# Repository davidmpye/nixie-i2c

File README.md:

# nixie-i2c

Nixie-I2C is a collection of PCB designs and accompanying library designed to simplify using [Nixie tubes](http://en.wikipedia.org/wiki/Nixie_tube) with Arduino and ESP8266 based boards (and perhaps others in future).

## Design

Driving nixie tubes from microcontrollers can present several issues:
 - Can rely on expensive/obsolute/irreplacable Soviet-era driver ICs (eg K155ID1)
 - Or, if you drive the cathodes directly, requires a large number of pins from the microcontroller (e.g a numeric IN-14 nixie tube has 12 cathodes - 0-9 and left/right decimal places), so it becomes difficult to direct-drive multiple tubes without running out of IO pins
 - If using the 'direct drive' solution above, you need a high-voltage capable transistor per cathode.
 
The main idea of this project is to provide a convenient driver board for a nixie tube, allowing it to be controlled from the microcontroller via I2C.

## Features

The PCB design here (which is tested and works) offers the following features:
 - Bus based (I2C) - put all your tubes in a row on stripboard or similar!
 - Designed for IN-14 nixie tube
 - I2C address (3-bit) settable (solder-pads on underside of board), allowing 9 nixie tubes per I2C bus.
 - Handles all HV switching, allowing a simple library interface to select the digit to be displayed.  Uses cheap SMD NPN transistors (MMBTA42s)
 - Has option for installing a programmable RGB (WS2812B) LED under the base of each tube, allowing bottom-lighting of any colour/brightness, without requiring ongoing control from the microcontroller (eg no PWM timing loops etc)
 - Eagle brd/sch files provided
 - Licenced under the OSHW framework
 
 There is an accompanying library, which supports:
 - Arduino or ESP8266
 - Simple interface to setting a tube's display digit / decimal point status
 - Slot-machine display for cathode protection
 - Direct drive for up to 9 tubes (per I2C bus), no multiplexing/timer loops from the microntroller required
 
##Example

 The library is designed to be simple and easy to use:
 ```
 Nixie_i2c nix0(0x00);
 nix0.slotMachineDisplayNumber(1);  //Tube now displays 1
 delay(1000);
 nix0.slotMachineDisplayNumber(9);  //Tube now displays 9
 ```

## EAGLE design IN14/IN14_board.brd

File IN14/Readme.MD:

#IN-14 Nixie Tube I2C PCB design

##Tech Specs:
- Overall dimensions: 24mm x  52.5mm
- Nixie tube centre point: 12mm (ie in the middle of the board in X), 12.3mm in from front edge
- Screw fixing centre 1: 3.25 from edge, 3.25 in from front of board
- Screw fixing centre 2: 3mm from other edge, 19.75mm in from front of board
- Screw hole size: M3
- Pinout(from front to rear):
- - +HV (~170VDC)
- - GND (Common between +HV and VCC)
- - LED_DATA_IN (signal 'in' to WS2812B)
- - LED_DATA_OUT (signal 'out' to next WS2812B in chain)
- - VCC (3.3-5VDC)
- - SCL  (single external 4k7 pull-UP resistor per bus advisable)
- - SDA  (single external 4k7 pull-UP resistor per bus advisable)

##Parts list:
###Top side of board:
- 1x IN-12 nixie tube
- 1x Nixie tube base (3d printable one available as STL file in this folder, with cutout for WS2812B LED)
- 1x WS2812B LED (optional but good!)
- 1x MCP23017 I2C multiplexer IC (SMD)
- 1x 0806 anode resistor 
- 3x 0604 4k7 SMD resistor arrays

##Hints

- Solder the resistor arrays in to place first (flood soldering works best)
- Solder the I2C multiplexer chips and other parts in to place
- Set the I2C address bits on the rear side of the board - bridging the middle and left pad sets the bit to 0, middle and right sets the bit to 1.  Bridging all three pins shorts VCC to GND!
- If mounting PCB to the case, it's best to use nylon bolts - reducing the risk of an electrical fault allowing the anode voltage appearing on the outside of a case!

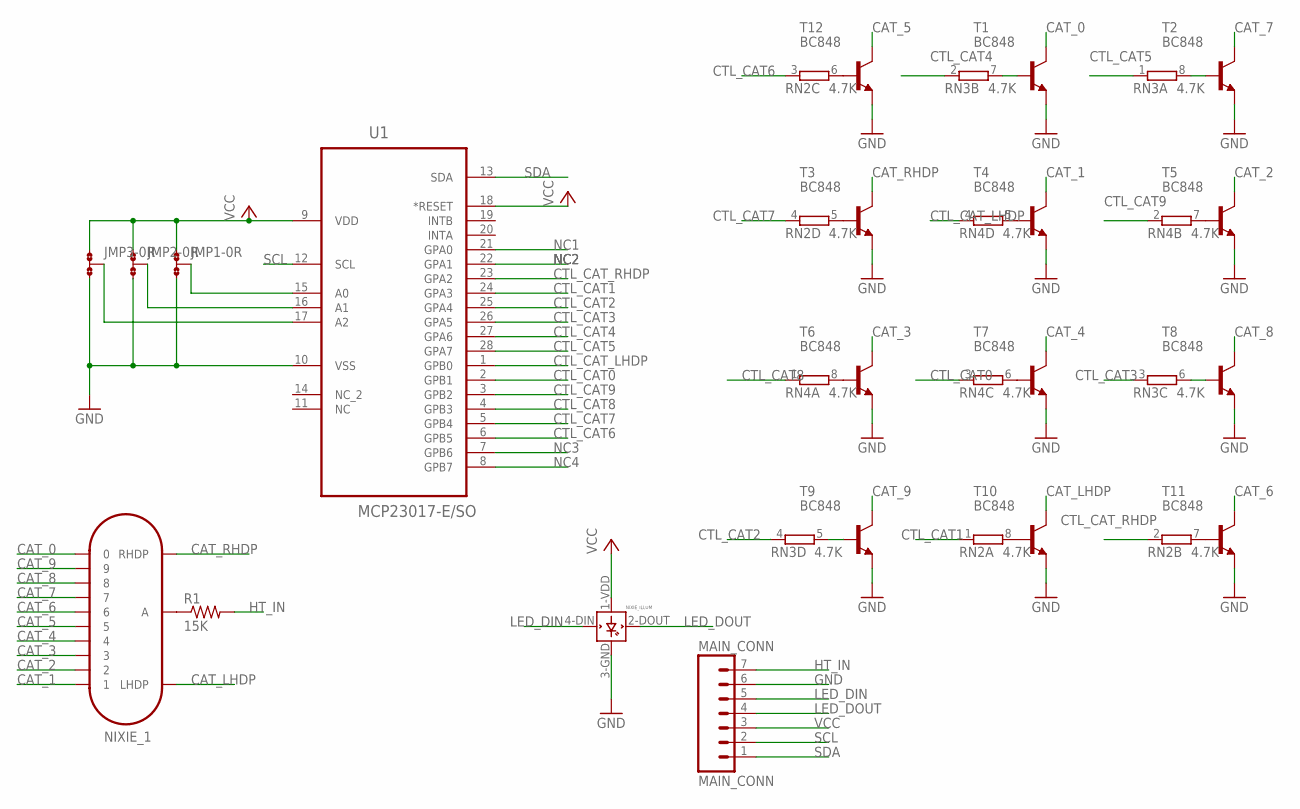
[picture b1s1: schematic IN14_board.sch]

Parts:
JMP1, JMP2, JMP3: 0R-JUMPA; A0R-JMP
MAIN_CONN: MAIN_CONN; 1X07_LONGPADS
NIXIE_1: IN-14
NIXIE_ILLUM: WS2812B
R1: 15K; 0603-RES
RN2, RN3, RN4: 4.7K; EXB38V
T1, T2, T3, T4, T5, T6, T7, T8, T9, T10, T11, T12: BC848; SOT23
U1: MCP23017-E/SO; SOIC127P1032X265-28N

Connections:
CAT_0: NIXIE_1.0, T1.3 (C)
CAT_1: NIXIE_1.1, T4.3 (C)
CAT_2: NIXIE_1.2, T5.3 (C)
CAT_3: NIXIE_1.3, T6.3 (C)
CAT_4: NIXIE_1.4, T7.3 (C)
CAT_5: NIXIE_1.5, T12.3 (C)
CAT_6: NIXIE_1.6, T11.3 (C)
CAT_7: NIXIE_1.7, T2.3 (C)
CAT_8: NIXIE_1.8, T8.3 (C)
CAT_9: NIXIE_1.9, T9.3 (C)
CAT_LHDP: NIXIE_1.LHDP, T10.3 (C)
CAT_RHDP: NIXIE_1.RHDP, T3.3 (C)
CTL_CAT0: RN4.3 (1), U1.2 (GPB1)
CTL_CAT1: RN2.1, U1.24 (GPA3)
CTL_CAT2: RN3.4 (1), U1.25 (GPA4)
CTL_CAT3: RN3.3 (1), U1.26 (GPA5)
CTL_CAT4: RN3.2 (1), U1.27 (GPA6)
CTL_CAT5: RN3.1, U1.28 (GPA7)
CTL_CAT6: RN2.3 (1), U1.6 (GPB5)
CTL_CAT7: RN2.4 (1), U1.5 (GPB4)
CTL_CAT8: RN4.1, U1.4 (GPB3)
CTL_CAT9: RN4.2 (1), U1.3 (GPB2)
CTL_CAT_LHDP: RN4.4 (1), U1.1 (GPB0)
CTL_CAT_RHDP: RN2.2 (1), U1.23 (GPA2)
GND: JMP1.3, JMP2.3, JMP3.3, MAIN_CONN.6, NIXIE_ILLUM.3-GND (GND), T1.2 (E), T2.2 (E), T3.2 (E), T4.2 (E), T5.2 (E), T6.2 (E), T7.2 (E), T8.2 (E), T9.2 (E), T10.2 (E), T11.2 (E), T12.2 (E), U1.10 (VSS)
HT_IN: MAIN_CONN.7, R1.2
LED_DIN: MAIN_CONN.5, NIXIE_ILLUM.4-DIN (DIN)
LED_DOUT: MAIN_CONN.4, NIXIE_ILLUM.2-DOUT (DOUT)
unnamed: RN3.8 (2), T2.1 (B)
unnamed: JMP1.2, U1.15 (A0)
unnamed: RN3.7 (2), T1.1 (B)
unnamed: NIXIE_1.A, R1.1
unnamed: RN3.6 (2), T8.1 (B)
unnamed: JMP2.2, U1.16 (A1)
unnamed: RN2.5 (2), T3.1 (B)
unnamed: JMP3.2, U1.17 (A2)
unnamed: RN4.5 (2), T4.1 (B)
unnamed: RN4.8 (2), T6.1 (B)
unnamed: RN3.5 (2), T9.1 (B)
unnamed: RN4.7 (2), T5.1 (B)
unnamed: RN4.6 (2), T7.1 (B)
unnamed: RN2.6 (2), T12.1 (B)
unnamed: RN2.7 (2), T11.1 (B)
unnamed: RN2.8 (2), T10.1 (B)
NC1: U1.21 (GPA0)
NC2: U1.22 (GPA1)
NC3: U1.7 (GPB6)
NC4: U1.8 (GPB7)
SCL: MAIN_CONN.2, U1.12 (SCL)
SDA: MAIN_CONN.1, U1.13 (SDA)
VCC: JMP1.1, JMP2.1, JMP3.1, MAIN_CONN.3, NIXIE_ILLUM.1-VDD (VDD), U1.9 (VDD), U1.18 (*RESET)

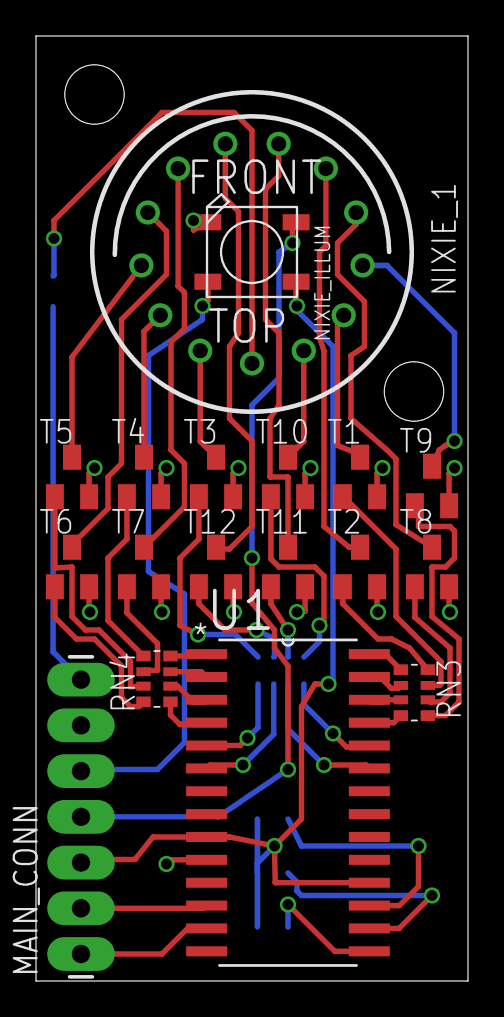
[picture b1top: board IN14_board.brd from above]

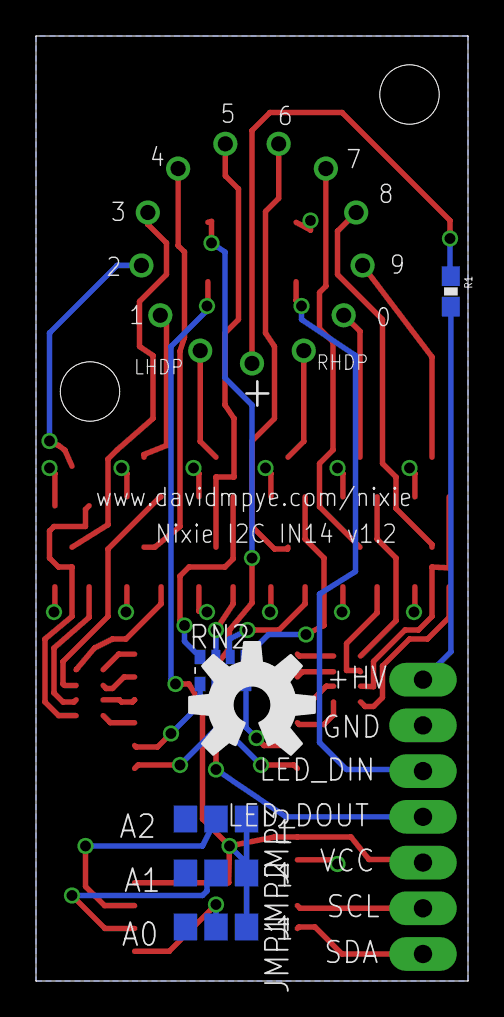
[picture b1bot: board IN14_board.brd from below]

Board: 2 copper layers, 24.0 x 52.5 mm, 26 parts (6 on the bottom side), 47 nets.

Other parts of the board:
U$1: OSHW-LOGO-L
U$2, U$5: STAND-OFF

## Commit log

2015-09-25 Initial import of IN14 boards
2015-09-25 Gerbers added
2015-09-26 IN14 3d printed bases added
2015-09-26 move dirs
2015-09-26 First draft of arduino library
2015-09-28 Fix includes/misnamed file
2015-09-28 More sensible slot machine change code
2016-03-24 Added files via upload
    New 'thinner' board - now revision 1.2. Pincompatible with previous bus-driven designs, but library code will need to be adjusted as the pins are mapped differently for economy of space!
2016-03-24 Added files via upload
    Move transistor down slightly to improve mounting hole clearance
2016-03-24 Added files via upload
    Moved a transistor for hole clearance improvement
2016-03-25 Moved files in together!
2016-03-25 New gerbers for 1.2v board
2016-04-02 Update for new PCB layout
2016-04-03 Add in example clock code
2016-04-17 Oops - fixed RHDP/LHDP mixup
2016-05-16 Update to add currentNumber functionality
2016-05-18 Fix bug where tube isn't initialised properly
2016-08-05 Add transistor detail

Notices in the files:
parts and their libraries:
SparkFun-Aesthetics: Licensing: Creative Commons ShareAlike 4.0 International - https://creativecommons.org/licenses/by-sa/4.0
